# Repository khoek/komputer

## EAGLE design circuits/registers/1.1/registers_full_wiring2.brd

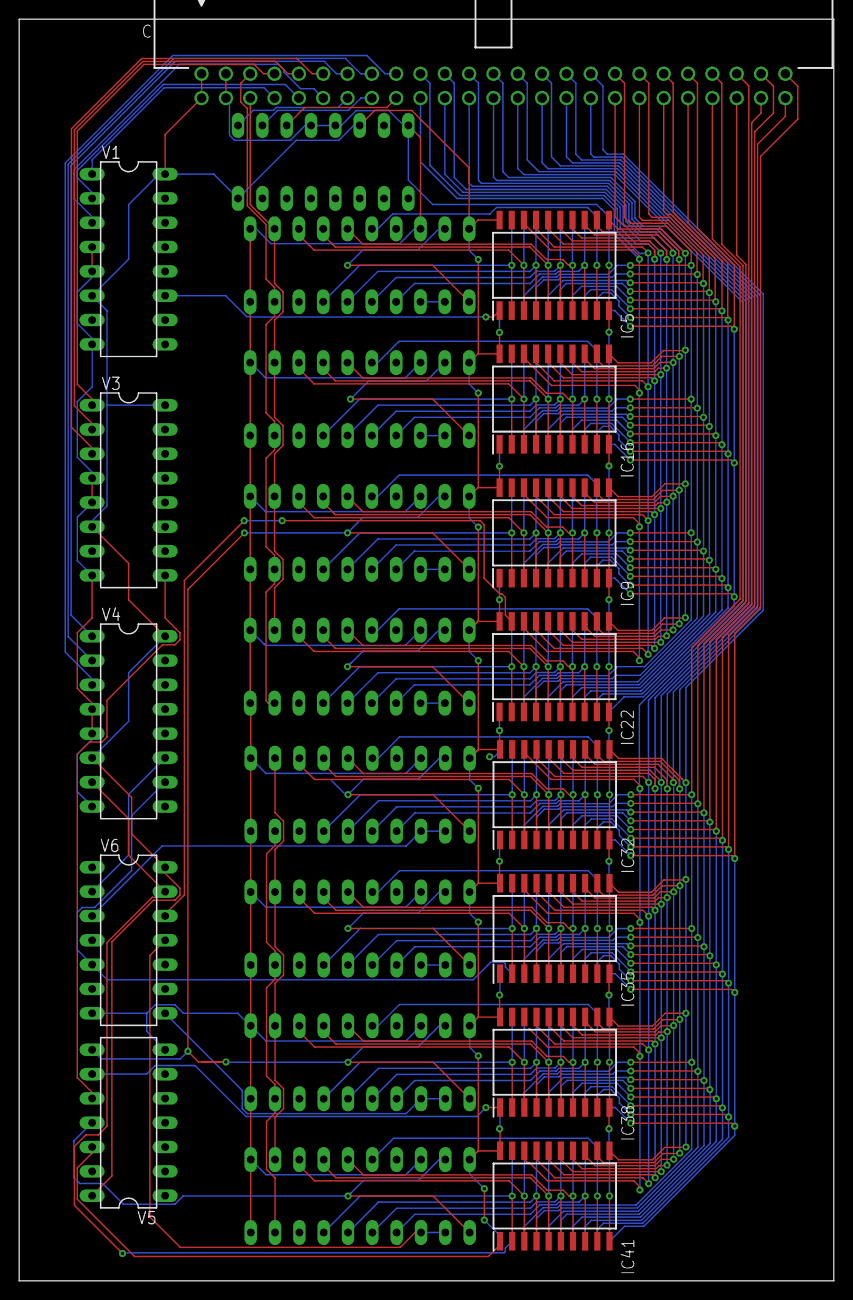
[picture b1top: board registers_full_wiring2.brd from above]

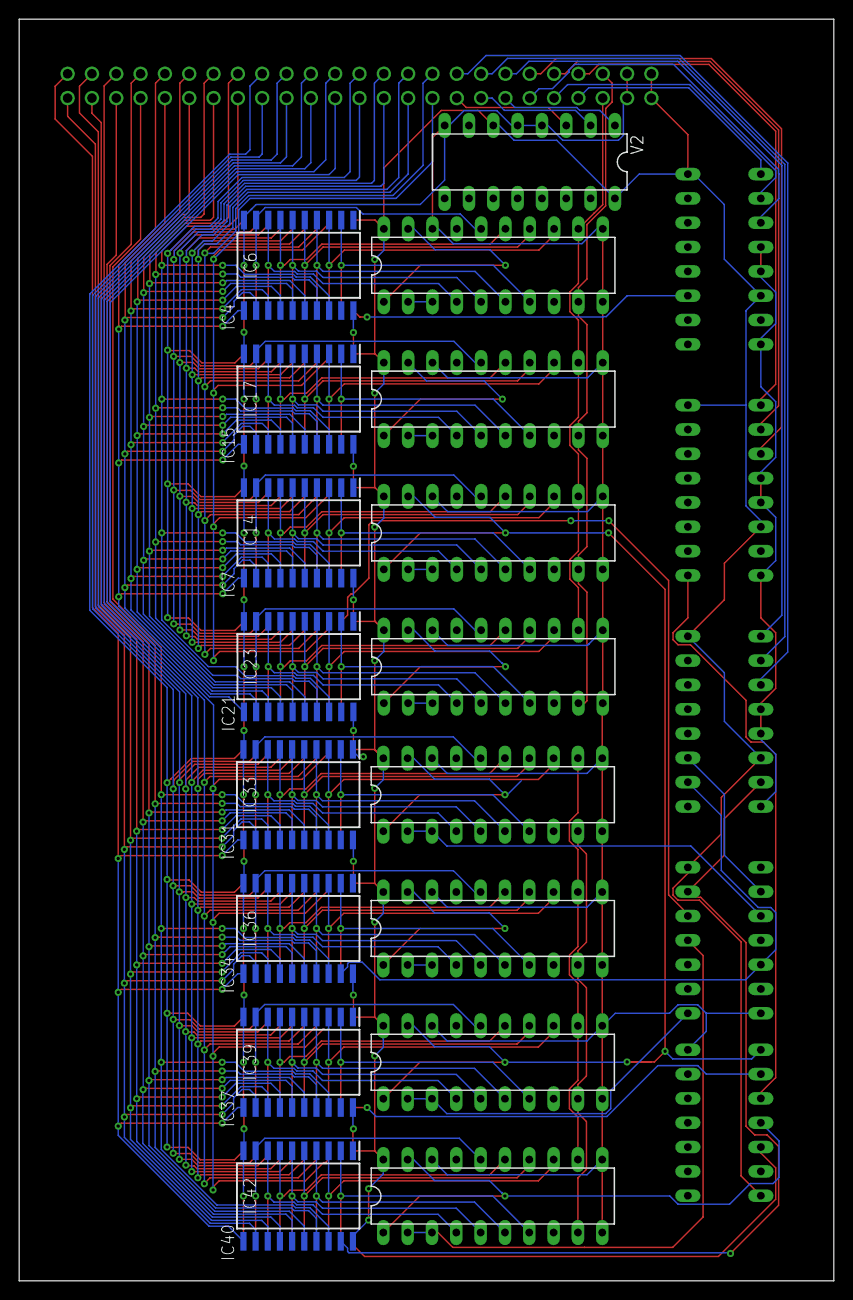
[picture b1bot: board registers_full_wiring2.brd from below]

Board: 2 copper layers, 85.1 x 131.8 mm, 31 parts (17 on the bottom side), 136 nets.

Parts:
C: 2550-5; PAK100/2500-5-50
IC4, IC7, IC15, IC21, IC31, IC34, IC37, IC40: 74HCT299N; DIL20
IC5, IC6, IC9, IC14, IC16, IC17, IC22, IC23, IC32, IC33, IC35, IC36, IC38, IC39, IC41, IC42: SN74CBT3345DW; SOIC127P1030X265-20N
V1, V3: 74238N; DIL16
V2, V4: 74138N; DIL16
V5: 7432N; DIL14
V6: 7408N; DIL14

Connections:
BUSA_BIT0: C.19, IC5.18, IC9.18, IC16.18, IC22.18
BUSA_BIT1: C.20, IC5.17, IC9.17, IC16.17, IC22.17
BUSA_BIT2: C.21, IC5.16, IC9.16, IC16.16, IC22.16
BUSA_BIT3: C.22, IC5.15, IC9.15, IC16.15, IC22.15
BUSA_BIT4: C.23, IC5.14, IC9.14, IC16.14, IC22.14
BUSA_BIT5: C.24, IC5.13, IC9.13, IC16.13, IC22.13
BUSA_BIT6: C.25, IC5.12, IC9.12, IC16.12, IC22.12
BUSA_BIT7: C.26, IC5.11, IC9.11, IC16.11, IC22.11
BUSA_BIT8: C.27, IC32.18, IC35.18, IC38.18, IC41.18
BUSA_BIT9: C.28, IC32.17, IC35.17, IC38.17, IC41.17
BUSA_BIT10: C.29, IC32.16, IC35.16, IC38.16, IC41.16
BUSA_BIT11: C.30, IC32.15, IC35.15, IC38.15, IC41.15
BUSA_BIT12: C.31, IC32.14, IC35.14, IC38.14, IC41.14
BUSA_BIT13: C.32, IC32.13, IC35.13, IC38.13, IC41.13
BUSA_BIT14: C.33, IC32.12, IC35.12, IC38.12, IC41.12
BUSA_BIT15: C.34, IC32.11, IC35.11, IC38.11, IC41.11
BUSA_REGIN0: C.7, V1.1
BUSA_REGIN1: C.9, V1.2
BUSA_REGIN2: C.11, V1.3
BUSA_REGOUT0: C.13, V2.1
BUSA_REGOUT1: C.15, V2.2
BUSA_REGOUT2: C.17, V2.3
BUSB_BIT0: C.35, IC6.18, IC14.18, IC17.18, IC23.18
BUSB_BIT1: C.36, IC6.17, IC14.17, IC17.17, IC23.17
BUSB_BIT2: C.37, IC6.16, IC14.16, IC17.16, IC23.16
BUSB_BIT3: C.38, IC6.15, IC14.15, IC17.15, IC23.15
BUSB_BIT4: C.39, IC6.14, IC14.14, IC17.14, IC23.14
BUSB_BIT5: C.40, IC6.13, IC14.13, IC17.13, IC23.13
BUSB_BIT6: C.41, IC6.12, IC14.12, IC17.12, IC23.12
BUSB_BIT7: C.42, IC6.11, IC14.11, IC17.11, IC23.11
BUSB_BIT8: C.43, IC33.18, IC36.18, IC39.18, IC42.18
BUSB_BIT9: C.44, IC33.17, IC36.17, IC39.17, IC42.17
BUSB_BIT10: C.45, IC33.16, IC36.16, IC39.16, IC42.16
BUSB_BIT11: C.46, IC33.15, IC36.15, IC39.15, IC42.15
BUSB_BIT12: C.47, IC33.14, IC36.14, IC39.14, IC42.14
BUSB_BIT13: C.48, IC33.13, IC36.13, IC39.13, IC42.13
BUSB_BIT14: C.49, IC33.12, IC36.12, IC39.12, IC42.12
BUSB_BIT15: C.50, IC33.11, IC36.11, IC39.11, IC42.11
BUSB_REGIN0: C.8, V3.1
BUSB_REGIN1: C.10, V3.2
BUSB_REGIN2: C.12, V3.3
BUSB_REGOUT0: C.14, V4.1
BUSB_REGOUT1: C.16, V4.2
BUSB_REGOUT2: C.18, V4.3
CLK: C.5, IC4.12, IC7.12, IC15.12, IC21.12, IC31.12, IC34.12, IC37.12, IC40.12
GND: C.3, C.4, IC4.10, IC4.11, IC4.18, IC5.10, IC6.10, IC7.10, IC7.11, IC7.18, IC9.10, IC14.10, IC15.10, IC15.11, IC15.18, IC16.10, IC17.10, IC21.10, IC21.11, IC21.18, IC22.10, IC23.10, IC31.10, IC31.11, IC31.18, IC32.10, IC33.10, IC34.10, IC34.11, IC34.18, IC35.10, IC36.10, IC37.10, IC37.11, IC37.18, IC38.10, IC39.10, IC40.10, IC40.11, IC40.18, IC41.10, IC42.10, V1.4, V1.5, V1.8, V2.4, V2.5, V2.8, V3.4, V3.5, V3.8, V4.4, V4.5, V4.8, V5.7, V6.7
unnamed: IC34.16, IC35.9, IC36.9
unnamed: IC16.1, IC35.1, V1.10, V5.4
unnamed: IC16.19, IC35.19, V2.10, V6.4
unnamed: IC4.2, IC4.3, IC31.2, IC31.3, V6.3
unnamed: IC4.7, IC5.2, IC6.2
unnamed: IC4.13, IC5.3, IC6.3
unnamed: IC4.6, IC5.4, IC6.4
unnamed: IC4.14, IC5.5, IC6.5
unnamed: IC4.5, IC5.6, IC6.6
unnamed: IC4.15, IC5.7, IC6.7
unnamed: IC4.4, IC5.8, IC6.8
unnamed: IC5.1, IC32.1, V1.11, V5.1
unnamed: IC5.19, IC32.19, V2.11, V6.1
unnamed: IC4.16, IC5.9, IC6.9
unnamed: IC6.19, IC33.19, V4.11, V6.2
unnamed: IC15.1, IC15.19, IC34.1, IC34.19, V5.6
unnamed: IC15.2, IC15.3, IC34.2, IC34.3, V6.6
unnamed: IC4.1, IC4.19, IC31.1, IC31.19, V5.3
unnamed: IC7.7, IC9.2, IC14.2
unnamed: IC7.13, IC9.3, IC14.3
unnamed: IC7.6, IC9.4, IC14.4
unnamed: IC7.14, IC9.5, IC14.5
unnamed: IC17.1, IC36.1, V3.10, V5.5
unnamed: IC17.19, IC36.19, V4.10, V6.5
unnamed: IC7.5, IC9.6, IC14.6
unnamed: IC14.1, IC39.1, V3.9, V5.10
unnamed: IC7.1, IC7.19, IC37.1, IC37.19, V5.8
unnamed: IC7.2, IC7.3, IC37.2, IC37.3, V6.8
unnamed: IC23.1, IC42.1, V3.7, V5.13
unnamed: IC9.1, IC38.1, V1.9, V5.9
unnamed: IC9.19, IC38.19, V2.9, V6.9
unnamed: IC7.15, IC9.7, IC14.7
unnamed: IC7.4, IC9.8, IC14.8
unnamed: IC7.16, IC9.9, IC14.9
unnamed: IC14.19, IC39.19, V4.9, V6.10
unnamed: IC15.7, IC16.2, IC17.2
unnamed: IC15.13, IC16.3, IC17.3
unnamed: IC15.6, IC16.4, IC17.4
unnamed: IC15.14, IC16.5, IC17.5
unnamed: IC15.5, IC16.6, IC17.6
unnamed: IC15.15, IC16.7, IC17.7
unnamed: IC15.4, IC16.8, IC17.8
unnamed: IC15.16, IC16.9, IC17.9
unnamed: IC21.1, IC21.19, IC40.1, IC40.19, V5.11
unnamed: IC22.1, IC41.1, V1.7, V5.12
unnamed: IC23.19, IC42.19, V4.7, V6.13
unnamed: IC22.19, IC41.19, V2.7, V6.12
unnamed: IC21.7, IC22.2, IC23.2
unnamed: IC21.13, IC22.3, IC23.3
unnamed: IC21.6, IC22.4, IC23.4
unnamed: IC21.14, IC22.5, IC23.5
unnamed: IC21.5, IC22.6, IC23.6
unnamed: IC21.15, IC22.7, IC23.7
unnamed: IC21.4, IC22.8, IC23.8
unnamed: IC21.16, IC22.9, IC23.9
unnamed: IC31.7, IC32.2, IC33.2
unnamed: IC31.13, IC32.3, IC33.3
unnamed: IC31.6, IC32.4, IC33.4
unnamed: IC31.14, IC32.5, IC33.5
unnamed: IC31.5, IC32.6, IC33.6
unnamed: IC31.15, IC32.7, IC33.7
unnamed: IC31.4, IC32.8, IC33.8
unnamed: IC31.16, IC32.9, IC33.9
unnamed: IC34.7, IC35.2, IC36.2
unnamed: IC34.13, IC35.3, IC36.3
unnamed: IC34.6, IC35.4, IC36.4
unnamed: IC34.14, IC35.5, IC36.5
unnamed: IC34.5, IC35.6, IC36.6
unnamed: IC34.15, IC35.7, IC36.7
unnamed: IC34.4, IC35.8, IC36.8
unnamed: IC37.7, IC38.2, IC39.2
unnamed: IC37.13, IC38.3, IC39.3
unnamed: IC37.6, IC38.4, IC39.4
unnamed: IC37.14, IC38.5, IC39.5
unnamed: IC37.5, IC38.6, IC39.6
unnamed: IC37.15, IC38.7, IC39.7
unnamed: IC37.4, IC38.8, IC39.8
unnamed: IC37.16, IC38.9, IC39.9
unnamed: IC40.7, IC41.2, IC42.2
unnamed: IC40.13, IC41.3, IC42.3
unnamed: IC40.6, IC41.4, IC42.4
unnamed: IC40.14, IC41.5, IC42.5
unnamed: IC21.2, IC21.3, IC40.2, IC40.3, V6.11
unnamed: IC40.5, IC41.6, IC42.6
unnamed: IC40.15, IC41.7, IC42.7
unnamed: IC40.4, IC41.8, IC42.8
unnamed: IC40.16, IC41.9, IC42.9
unnamed: IC6.1, IC33.1, V3.11, V5.2
STARTUP: C.6, IC4.9, IC7.9, IC15.9, IC21.9, IC31.9, IC34.9, IC37.9, IC40.9
VCC: C.1, C.2, IC4.20, IC5.20, IC6.20, IC7.20, IC9.20, IC14.20, IC15.20, IC16.20, IC17.20, IC21.20, IC22.20, IC23.20, IC31.20, IC32.20, IC33.20, IC34.20, IC35.20, IC36.20, IC37.20, IC38.20, IC39.20, IC40.20, IC41.20, IC42.20, V1.6, V1.16, V2.6, V2.16, V3.6, V3.16, V4.6, V4.16, V5.14, V6.14
